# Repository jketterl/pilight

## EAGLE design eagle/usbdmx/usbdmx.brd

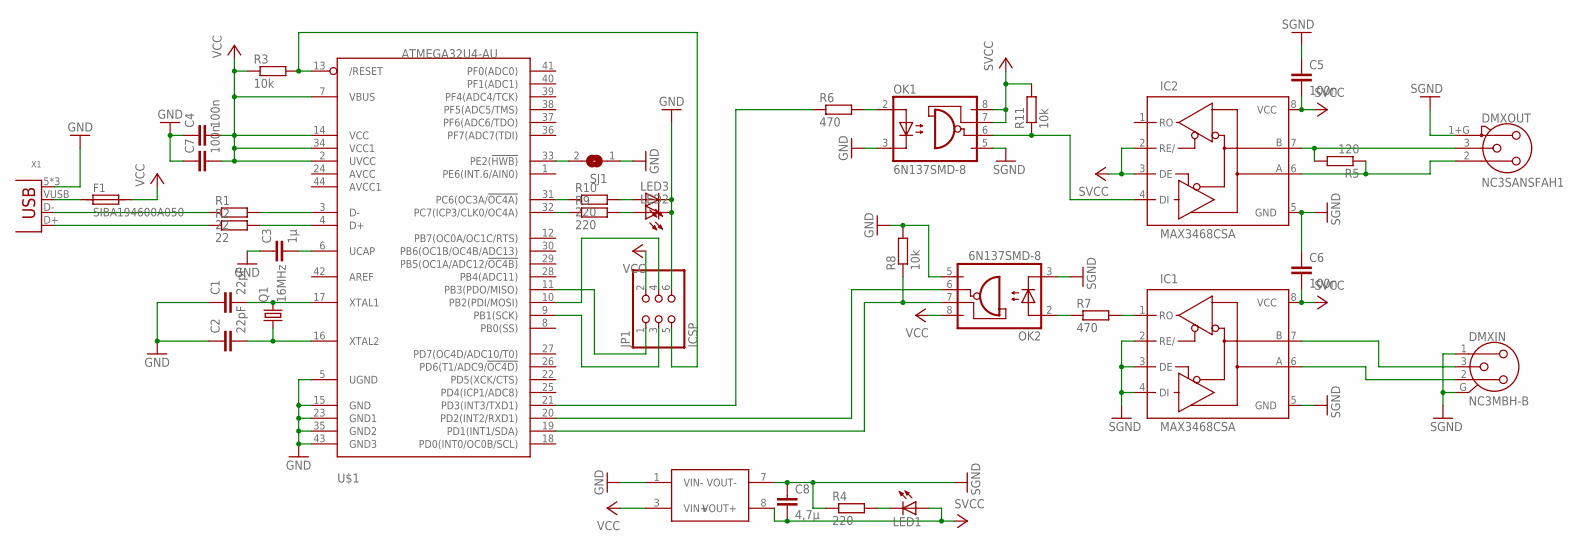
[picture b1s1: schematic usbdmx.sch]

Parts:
C1, C2: 22pF; C0805
C3: 1µ; C0805
C4, C5, C6, C7: 100n; C0805
C8: 4,7µ; C0805
DMXIN: NC3MBH-B
DMXOUT: NC3SANSFAH1; NC3FAH1
F1: SIBA194600A050; 1820
IC1, IC2: MAX3468CSA; SO08
JP1: ICSP; 2X03SMD
LED1, LED2, LED3: LEDSML0603; SML0603
OK1, OK2: 6N137SMD-8; SMD8
Q1: 16MHz; MT
R1, R2: 22; R0805
R3, R8, R11: 10k; R0805
R4, R9, R10: 220; R0805
R5: 120; R0805
R6, R7: 470; R0805
SJ1: SJ
U$1: ATMEGA32U4-AU; TQFP44
U$2: NTE0505SNTE0505MEC; SMT
X1: USB-B-S-R; USB-B-SMT-R

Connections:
GND: C1.1, C2.1, C3.1, C4.1, C7.1, JP1.6, LED2.C, LED3.C, OK1.3 (C), OK2.5 (GND), R8.2, SJ1.1, U$1.5 (UGND), U$1.15 (GND), U$1.23 (GND1), U$1.35 (GND2), U$1.43 (GND3), U$2.1 (VIN-), X1.5 (GND), X1.6 (GND), X1.GND
unnamed: C1.2, Q1.P3 (2), U$1.17 (XTAL1)
unnamed: C2.2, Q1.P1 (1), U$1.16 (XTAL2)
unnamed: R1.2, U$1.3 (D-)
unnamed: R2.2, U$1.4 (D+)
unnamed: R2.1, X1.D+
unnamed: R1.1, X1.D-
unnamed: F1.1, X1.VUSB (VBUS)
unnamed: C3.2, U$1.6 (UCAP)
unnamed: JP1.5, R3.2, U$1.13 (/RESET)
unnamed: R6.1, U$1.21 (PD3(INT3/TXD1))
unnamed: LED1.C, R4.2
unnamed: DMXOUT.2, IC2.6 (A), R5.1
unnamed: JP1.1, U$1.11 (PB3(PDO/MISO))
unnamed: JP1.4, U$1.10 (PB2(PDI/MOSI))
unnamed: JP1.3, U$1.9 (PB1(SCK))
unnamed: OK2.7 (VE), R8.1, U$1.19 (PD1(INT1/SDA))
unnamed: DMXOUT.3, IC2.7 (B), R5.2
unnamed: DMXIN.2, IC1.6 (A)
unnamed: SJ1.2, U$1.33 (PE2(!HWB))
unnamed: IC2.4 (DI), OK1.6 (VO), R11.1
unnamed: IC1.1 (RO), R7.2
unnamed: LED3.A, R10.2
unnamed: OK2.2 (A), R7.1
unnamed: OK2.6 (VO), U$1.20 (PD2(INT2/RXD1))
unnamed: OK1.2 (A), R6.2
unnamed: LED2.A, R9.2
unnamed: R9.1, U$1.32 (PC7(ICP3/CLK0/OC4A))
unnamed: R10.1, U$1.31 (PC6(OC3A/!OC4A))
unnamed: DMXIN.3, IC1.7 (B)
SGND: C5.1, C6.1, C8.1, DMXIN.1, DMXIN.G, DMXOUT.1+G (1), IC1.2 (RE/), IC1.3 (DE), IC1.4 (DI), IC1.5 (GND), IC2.5 (GND), OK1.5 (GND), OK2.3 (C), R4.1, U$2.7 (VOUT-)
SVCC: C5.2, C6.2, C8.2, IC1.8 (VCC), IC2.2 (RE/), IC2.3 (DE), IC2.8 (VCC), LED1.A, OK1.7 (VE), OK1.8 (VCC), R11.2, U$2.8 (VOUT+)
VCC: C4.2, C7.2, F1.2, JP1.2, OK2.8 (VCC), R3.1, U$1.2 (UVCC), U$1.7 (VBUS), U$1.14 (VCC), U$1.34 (VCC1), U$2.3 (VIN+)

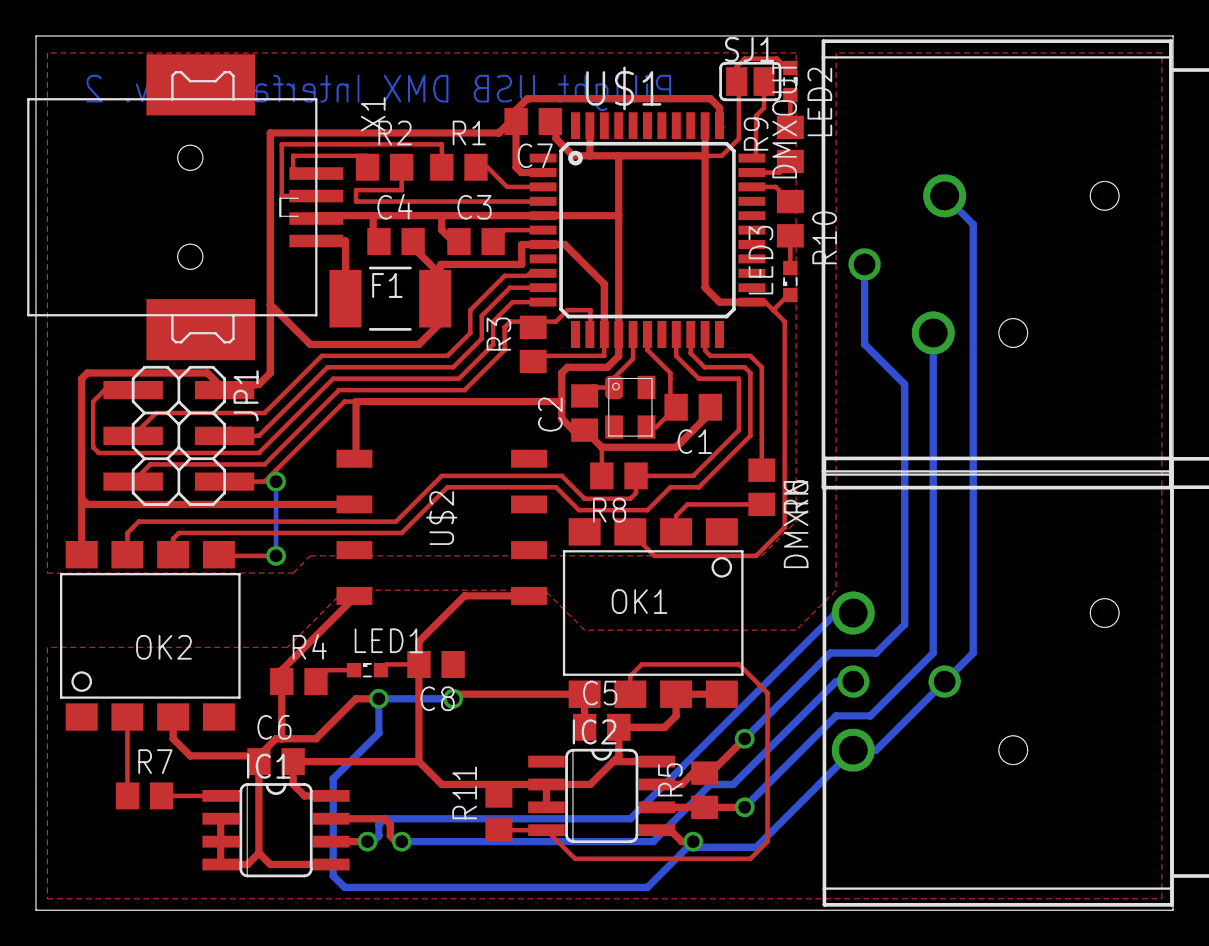
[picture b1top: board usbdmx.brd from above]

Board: 2 copper layers, 63.2 x 48.6 mm, 35 parts (0 on the bottom side), 33 nets.

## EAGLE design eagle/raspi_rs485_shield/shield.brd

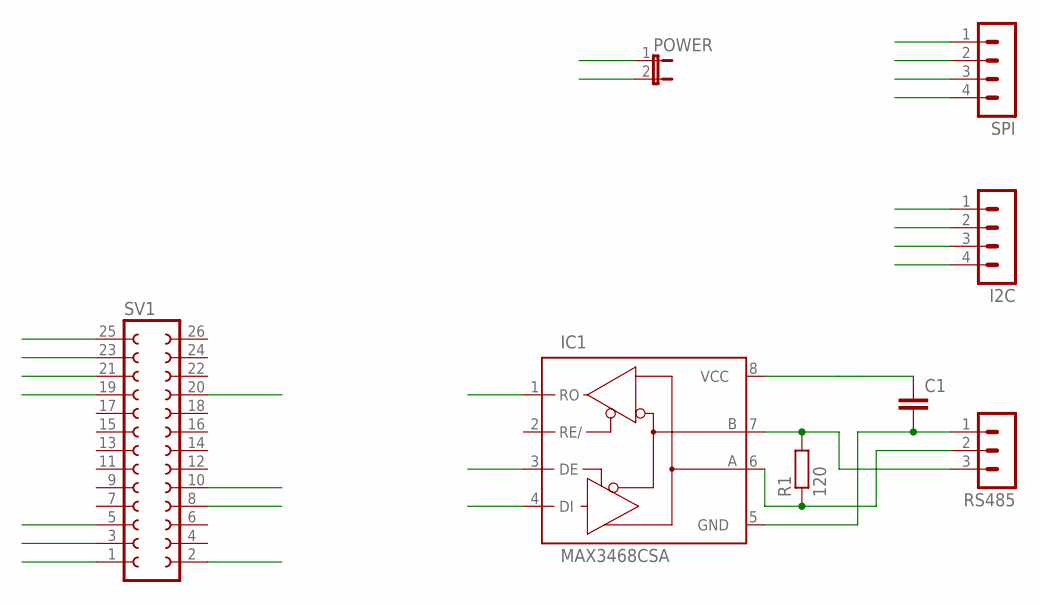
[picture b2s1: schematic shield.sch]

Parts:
C1: C-EUC0805; C0805
I2C: MA04-1
IC1: MAX3468CSA; SO08
POWER: JP1E; JP1
R1: 120; 0207/2V
RS485: MA03-1
SPI: MA04-1
SV1: FE13-2

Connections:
3V3: C1.1, IC1.3 (DE), IC1.8 (VCC), SV1.1
5V0: I2C.4, POWER.2, SV1.2
GND: C1.2, I2C.1, IC1.5 (GND), POWER.1, RS485.1, SPI.1, SV1.20, SV1.25
MISO: SPI.3, SV1.21
MOSI: SPI.2, SV1.19
unnamed: IC1.6 (A), R1.1, RS485.2
unnamed: IC1.7 (B), R1.2, RS485.3
RX: IC1.1 (RO), SV1.10
SCL: I2C.2, SV1.5
SCLK: SPI.4, SV1.23
SDA: I2C.3, SV1.3
TX: IC1.4 (DI), SV1.8

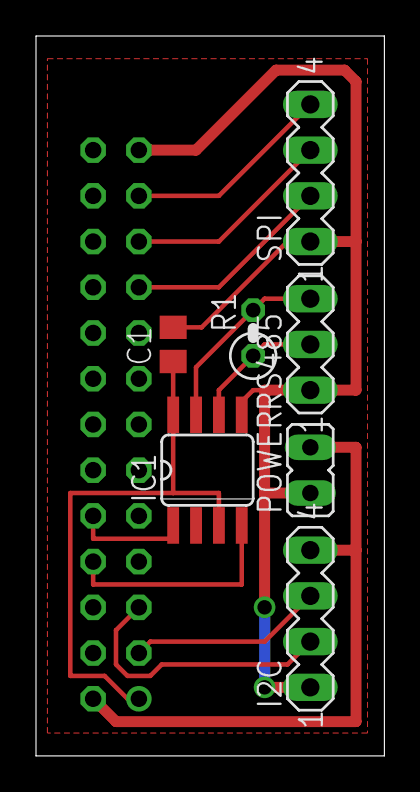
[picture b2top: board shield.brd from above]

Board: 2 copper layers, 19.4 x 40.0 mm, 8 parts (1 on the bottom side), 12 nets.

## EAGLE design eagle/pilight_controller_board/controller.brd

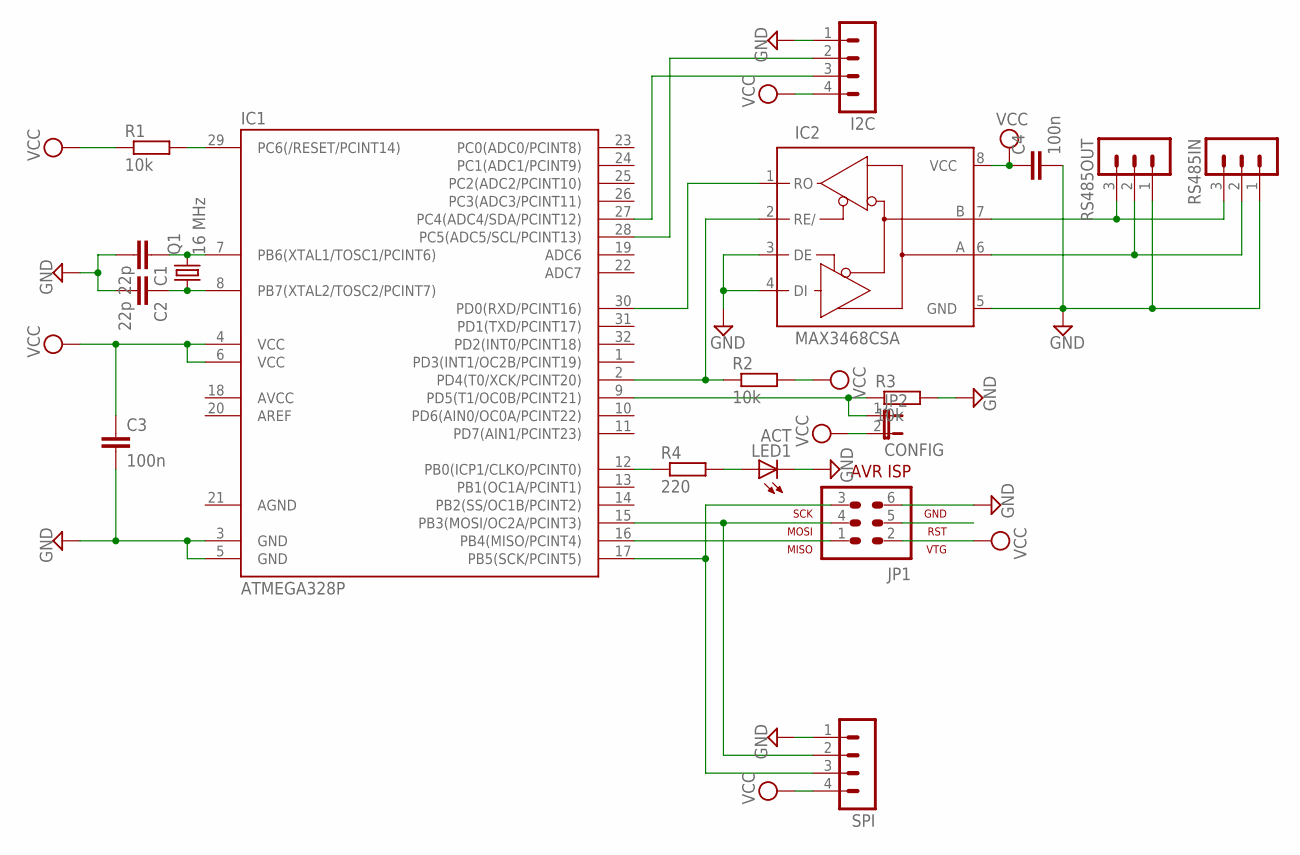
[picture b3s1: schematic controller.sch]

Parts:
C1, C2: 22p; C0805
C3, C4: 100n; C0805
I2C: MA04-1
IC1: ATMEGA328P; TQFP32-08
IC2: MAX3468CSA; SO08
JP1: AVR-ISP-6
JP2: CONFIG; JP1
LED1: ACT; SML0603
Q1: 16 MHz; MT
R1, R2, R3: 10k; R0805
R4: 220; R0805
RS485IN, RS485OUT: MA03-1
SPI: MA04-1

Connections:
AGND: IC1.21 (AGND)
GND: C1.2, C2.2, C3.2, C4.2, I2C.1, IC1.3 (GND), IC1.5 (GND), IC2.3 (DE), IC2.4 (DI), IC2.5 (GND), JP1.6, LED1.C, R3.2, RS485IN.1, RS485OUT.1, SPI.1
unnamed: IC1.30 (PD0(RXD/PCINT16)), IC2.1 (RO)
unnamed: IC1.15 (PB3(MOSI/OC2A/PCINT3)), JP1.4, SPI.2
unnamed: C1.1, IC1.7 (PB6(XTAL1/TOSC1/PCINT6)), Q1.P3 (2)
unnamed: C2.1, IC1.8 (PB7(XTAL2/TOSC2/PCINT7)), Q1.P1 (1)
unnamed: IC1.16 (PB4(MISO/PCINT4)), JP1.1
unnamed: IC1.17 (PB5(SCK/PCINT5)), JP1.3, SPI.3
unnamed: IC2.6 (A), RS485IN.2, RS485OUT.2
unnamed: IC2.7 (B), RS485IN.3, RS485OUT.3
unnamed: I2C.2, IC1.28 (PC5(ADC5/SCL/PCINT13))
unnamed: I2C.3, IC1.27 (PC4(ADC4/SDA/PCINT12))
unnamed: IC1.2 (PD4(T0/XCK/PCINT20)), IC2.2 (RE/), R2.1
unnamed: IC1.9 (PD5(T1/OC0B/PCINT21)), JP2.1, R3.1
unnamed: IC1.12 (PB0(ICP1/CLKO/PCINT0)), R4.1
unnamed: LED1.A, R4.2
RESET: IC1.29 (PC6(/RESET/PCINT14)), JP1.5, R1.2
VCC: C3.1, C4.1, I2C.4, IC1.4 (VCC), IC1.6 (VCC), IC2.8 (VCC), JP1.2, JP2.2, R1.1, R2.2, SPI.4

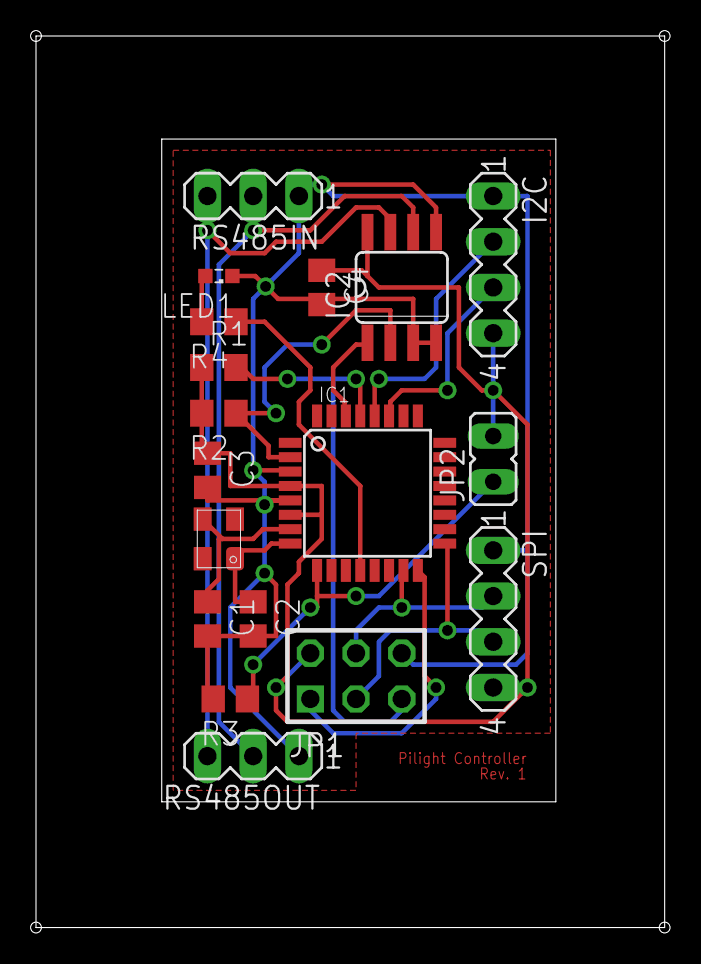
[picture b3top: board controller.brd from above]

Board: 2 copper layers, 34.9 x 49.5 mm, 18 parts (0 on the bottom side), 17 nets.

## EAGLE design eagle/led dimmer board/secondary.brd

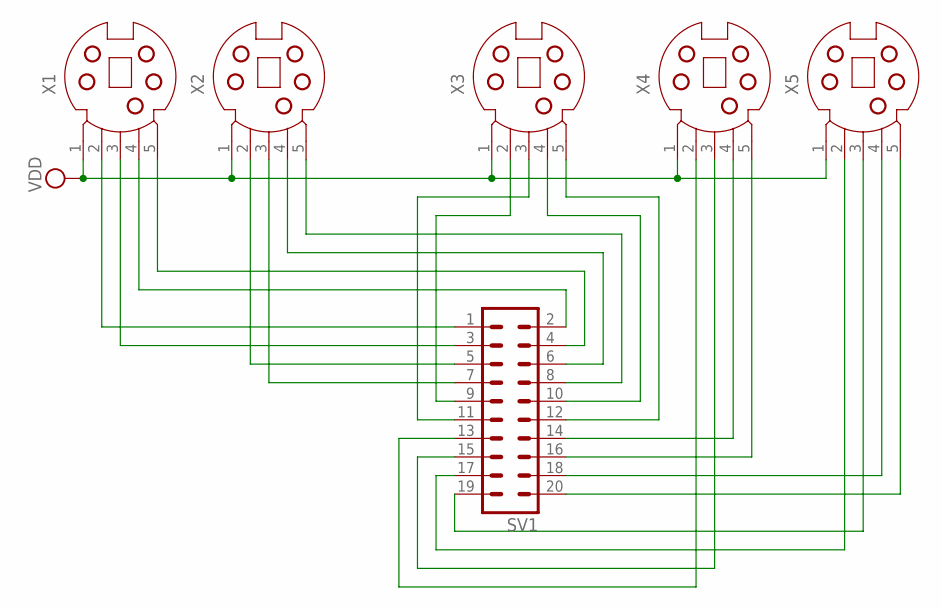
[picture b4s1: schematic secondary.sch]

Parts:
SV1: MA10-2
X1, X2, X3, X4, X5: MD05S; MDIN05S

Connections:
unnamed: SV1.1, X1.2
unnamed: SV1.2, X1.4
unnamed: SV1.3, X1.3
unnamed: SV1.4, X1.5
unnamed: SV1.5, X2.2
unnamed: SV1.6, X2.4
unnamed: SV1.7, X2.3
unnamed: SV1.8, X2.5
unnamed: SV1.9, X3.2
unnamed: SV1.10, X3.4
unnamed: SV1.11, X3.3
unnamed: SV1.12, X3.5
unnamed: SV1.14, X4.4
unnamed: SV1.16, X4.5
unnamed: SV1.18, X5.4
unnamed: SV1.20, X5.5
unnamed: SV1.19, X5.3
unnamed: SV1.17, X5.2
unnamed: SV1.15, X4.3
unnamed: SV1.13, X4.2
VDD: X1.1, X2.1, X3.1, X4.1, X5.1

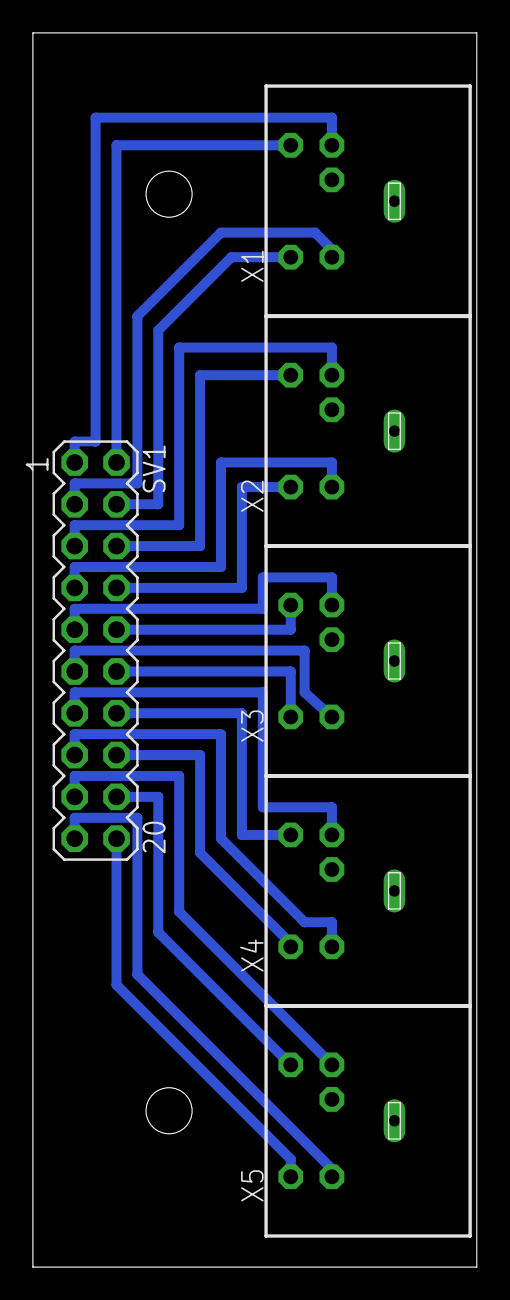
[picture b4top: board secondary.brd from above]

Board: 2 copper layers, 27.0 x 75.0 mm, 6 parts (0 on the bottom side), 21 nets.

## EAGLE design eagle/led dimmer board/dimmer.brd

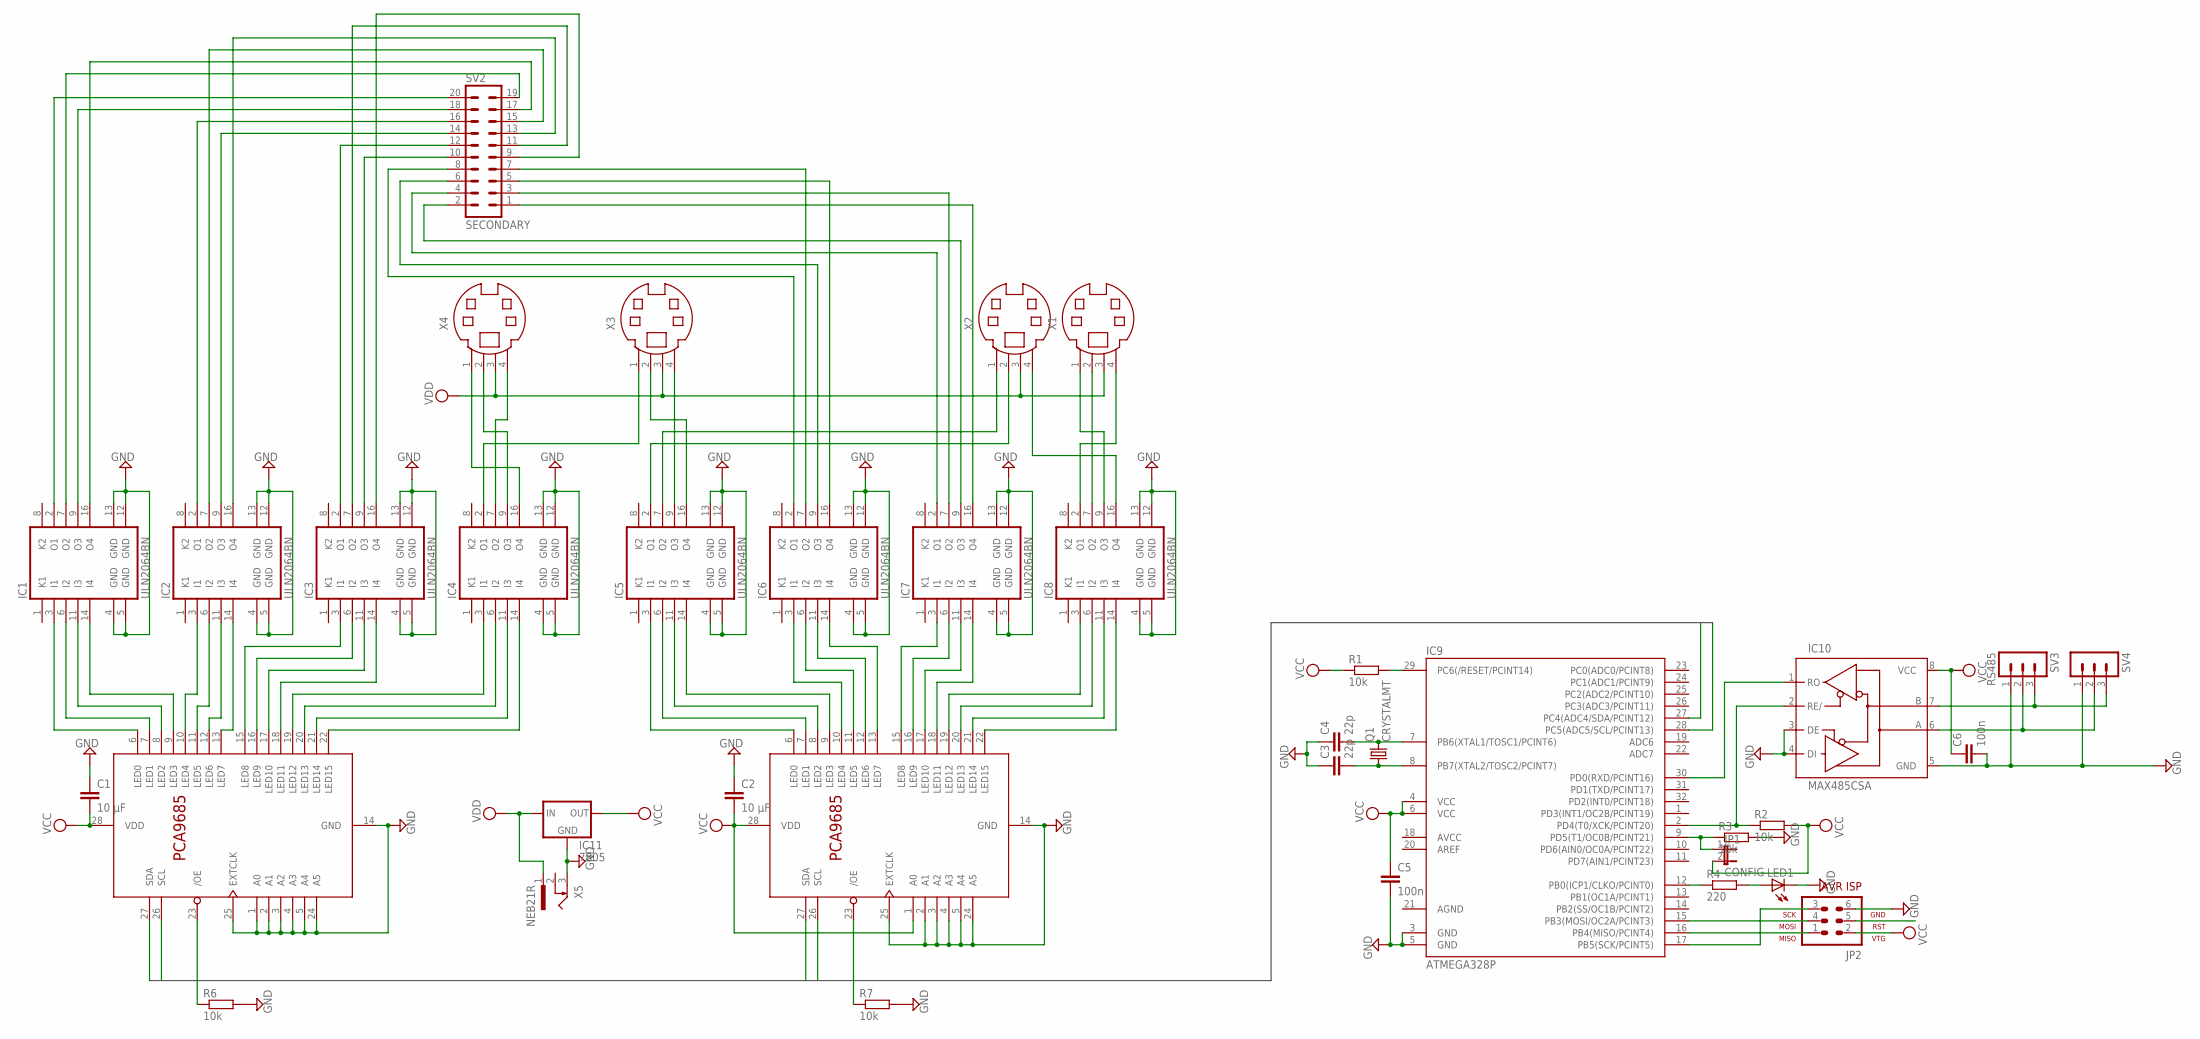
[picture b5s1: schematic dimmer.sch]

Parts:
C1, C2: 10 µF; C0805
C3, C4: 22p; C0805
C5, C6: 100n; C0805
IC1, IC2, IC3, IC4, IC5, IC6, IC7, IC8: ULN2064BN; DIL16
IC9: ATMEGA328P; TQFP32-08
IC10: MAX485CSA; SO08
IC11: 7805; 78XXS
JP1: CONFIG; JP1
JP2: AVR-ISP-6
LED1: LEDCHIP-LED0603; CHIP-LED0603
Q1: CRYSTALMT; MT
R1, R2, R3, R6, R7: 10k; R0805
R4: 220; R0805
SV2: SECONDARY; MA10-2
SV3: RS485; MA03-1
SV4: MA03-1
U$1, U$2: PCA9685PW; TSSOP28
X1, X2, X3, X4: MD04S; MDIN04S
X5: NEB21R

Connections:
AGND: IC9.21 (AGND)
GND: C1.1, C2.1, C3.1, C4.1, C5.2, C6.2, IC1.4 (GND), IC1.5 (GND), IC1.12 (GND), IC1.13 (GND), IC2.4 (GND), IC2.5 (GND), IC2.12 (GND), IC2.13 (GND), IC3.4 (GND), IC3.5 (GND), IC3.12 (GND), IC3.13 (GND), IC4.4 (GND), IC4.5 (GND), IC4.12 (GND), IC4.13 (GND), IC5.4 (GND), IC5.5 (GND), IC5.12 (GND), IC5.13 (GND), IC6.4 (GND), IC6.5 (GND), IC6.12 (GND), IC6.13 (GND), IC7.4 (GND), IC7.5 (GND), IC7.12 (GND), IC7.13 (GND), IC8.4 (GND), IC8.5 (GND), IC8.12 (GND), IC8.13 (GND), IC9.3 (GND), IC9.5 (GND), IC10.3 (DE), IC10.4 (DI), IC10.5 (GND), IC11.GND, JP2.6, LED1.C, R3.2, R6.2, R7.2, SV3.1, SV4.1, U$1.1 (A0), U$1.2 (A1), U$1.3 (A2), U$1.4 (A3), U$1.5 (A4), U$1.14 (GND), U$1.24 (A5), U$1.25 (EXTCLK), U$2.2 (A1), U$2.3 (A2), U$2.4 (A3), U$2.5 (A4), U$2.14 (GND), U$2.24 (A5), U$2.25 (EXTCLK), X5.3
unnamed: IC1.3 (I1), U$1.6 (LED0)
unnamed: IC1.6 (I2), U$1.7 (LED1)
unnamed: IC1.11 (I3), U$1.8 (LED2)
unnamed: IC1.14 (I4), U$1.9 (LED3)
unnamed: IC4.14 (I4), U$1.22 (LED15)
unnamed: IC4.11 (I3), U$1.21 (LED14)
unnamed: IC4.6 (I2), U$1.20 (LED13)
unnamed: IC4.3 (I1), U$1.19 (LED12)
unnamed: IC3.14 (I4), U$1.18 (LED11)
unnamed: IC3.11 (I3), U$1.17 (LED10)
unnamed: IC3.6 (I2), U$1.16 (LED9)
unnamed: IC3.3 (I1), U$1.15 (LED8)
unnamed: IC2.14 (I4), U$1.13 (LED7)
unnamed: IC2.11 (I3), U$1.12 (LED6)
unnamed: IC2.6 (I2), U$1.11 (LED5)
unnamed: IC2.3 (I1), U$1.10 (LED4)
unnamed: IC7.14 (I4), U$2.18 (LED11)
unnamed: IC5.6 (I2), U$2.7 (LED1)
unnamed: IC5.11 (I3), U$2.8 (LED2)
unnamed: IC5.14 (I4), U$2.9 (LED3)
unnamed: IC5.3 (I1), U$2.6 (LED0)
unnamed: IC6.3 (I1), U$2.10 (LED4)
unnamed: IC6.6 (I2), U$2.11 (LED5)
unnamed: IC6.11 (I3), U$2.12 (LED6)
unnamed: IC6.14 (I4), U$2.13 (LED7)
unnamed: IC8.14 (I4), U$2.22 (LED15)
unnamed: IC8.11 (I3), U$2.21 (LED14)
unnamed: IC8.6 (I2), U$2.20 (LED13)
unnamed: IC8.3 (I1), U$2.19 (LED12)
unnamed: IC7.11 (I3), U$2.17 (LED10)
unnamed: IC7.6 (I2), U$2.16 (LED9)
unnamed: IC7.3 (I1), U$2.15 (LED8)
unnamed: IC8.2 (O1), X1.4
unnamed: IC8.7 (O2), X1.2
unnamed: IC8.9 (O3), X1.1
unnamed: R6.1, U$1.23 (/OE)
unnamed: IC8.16 (O4), X2.4
unnamed: IC5.2 (O1), X2.2
unnamed: IC5.7 (O2), X2.1
unnamed: IC5.9 (O3), X3.4
unnamed: IC5.16 (O4), X3.2
unnamed: IC4.2 (O1), X3.1
unnamed: IC4.7 (O2), X4.4
unnamed: IC4.9 (O3), X4.2
unnamed: IC4.16 (O4), X4.1
unnamed: IC1.2 (O1), SV2.20
unnamed: IC1.7 (O2), SV2.19
unnamed: IC1.9 (O3), SV2.18
unnamed: IC1.16 (O4), SV2.17
unnamed: IC2.2 (O1), SV2.16
unnamed: IC2.7 (O2), SV2.15
unnamed: IC2.9 (O3), SV2.14
unnamed: IC2.16 (O4), SV2.13
unnamed: IC3.2 (O1), SV2.12
unnamed: IC3.7 (O2), SV2.11
unnamed: IC3.9 (O3), SV2.10
unnamed: IC3.16 (O4), SV2.9
unnamed: IC6.2 (O1), SV2.8
unnamed: IC6.7 (O2), SV2.7
unnamed: IC6.9 (O3), SV2.6
unnamed: IC6.16 (O4), SV2.5
unnamed: IC7.2 (O1), SV2.4
unnamed: IC7.7 (O2), SV2.3
unnamed: IC7.9 (O3), SV2.2
unnamed: IC7.16 (O4), SV2.1
unnamed: R7.1, U$2.23 (/OE)
unnamed: C4.2, IC9.7 (PB6(XTAL1/TOSC1/PCINT6)), Q1.P3 (2)
unnamed: IC9.30 (PD0(RXD/PCINT16)), IC10.1 (RO)
unnamed: C3.2, IC9.8 (PB7(XTAL2/TOSC2/PCINT7)), Q1.P1 (1)
unnamed: IC10.6 (A), SV3.2, SV4.2
unnamed: IC10.7 (B), SV3.3, SV4.3
unnamed: IC9.2 (PD4(T0/XCK/PCINT20)), IC10.2 (RE/), R2.1
unnamed: IC9.9 (PD5(T1/OC0B/PCINT21)), JP1.1, R3.1
unnamed: IC9.12 (PB0(ICP1/CLKO/PCINT0)), R4.1
unnamed: LED1.A, R4.2
unnamed: IC9.17 (PB5(SCK/PCINT5)), JP2.3
unnamed: IC9.16 (PB4(MISO/PCINT4)), JP2.1
unnamed: IC9.15 (PB3(MOSI/OC2A/PCINT3)), JP2.4
RESET: IC9.29 (PC6(/RESET/PCINT14)), JP2.5, R1.2
SCL: IC9.28 (PC5(ADC5/SCL/PCINT13)), U$1.26 (SCL), U$2.26 (SCL)
SDA: IC9.27 (PC4(ADC4/SDA/PCINT12)), U$1.27 (SDA), U$2.27 (SDA)
VCC: C1.2, C2.2, C5.1, C6.1, IC9.4 (VCC), IC9.6 (VCC), IC10.8 (VCC), IC11.OUT, JP1.2, JP2.2, R1.1, R2.2, U$1.28 (VDD), U$2.1 (A0), U$2.28 (VDD)
VDD: IC11.IN, X1.3, X2.3, X3.3, X4.3, X5.1

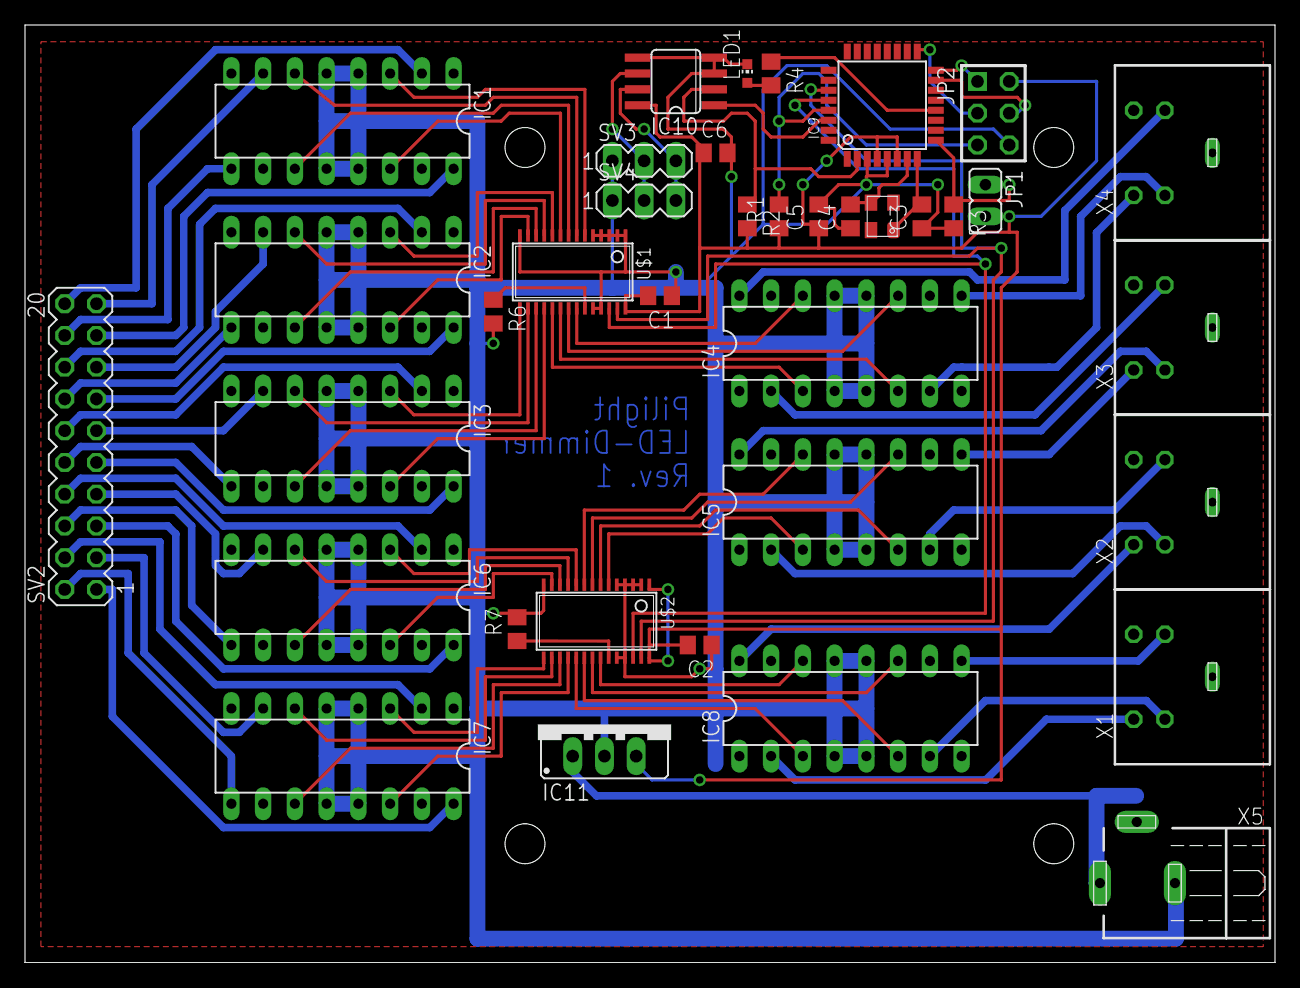
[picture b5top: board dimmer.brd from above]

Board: 2 copper layers, 100.0 x 75.0 mm, 37 parts (0 on the bottom side), 84 nets.

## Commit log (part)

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2012-11-07 initial import
2012-11-15 constructing an output module
2012-11-15 threaded output prototype
2012-11-15 drop the changes once written
2012-11-16 adding LPD8806 support
2012-11-16 add flush to make it work
2012-11-16 let's get some action :)
2012-11-16 fix typos
2012-11-16 fix channel count
2012-11-16 add the knight rider
2012-11-18 test for "None" value before pushing changes out
2012-11-18 write out some extra zeros to flush
2012-11-18 add snowflakes :)
2012-11-18 fix indentation
2012-11-19 implement the knight rider OOP
2012-11-19 add new VU Meter show
2012-11-19 move to the right location
2012-11-19 fix colors
2012-11-19 trying to get the vu meter running
2012-11-19 fixing audio reading by putting it into a background thread
2012-11-20 performance optimizing the vu meter
2012-11-20 make the vu meter smoother by introducing a smoothing thread
2012-11-20 commit uncomplete changes (so far, so good)
2012-11-20 lots of changes to improve the vu meter (better refresh rate, improved smoothin)
2012-11-21 refactor: create audio module & move the audioreader over
2012-11-21 move over the analyzer too
2012-11-21 no longer a show object
2012-11-21 simulating a bpm show (with constant "heartbeat" as bpm)
2012-11-21 integrate bpm show
2012-11-21 move sanity check to the reader
2012-11-21 clean up after show end
2012-11-21 incomplete beat detection
2012-11-22 fix a potential issue with empty data
2012-11-22 refactor audioreader to be reusable
2012-11-22 fixed beatdetection (unpacked wrong)
2012-11-23 fft-based beat-detection, phase 1
2012-11-25 fiddling with the BeatDetector code implementing first steps with lirc
2012-11-25 further lirc control
2012-11-25 more shows
2012-11-25 multi-key-mapping standby code
2012-11-25 add the fixtures parameter as a default to all shows
2012-11-25 re-implement the snowflake show as a show
2012-11-25 ignore compiled python files
2012-11-25 faster clearup interval (in case of disturbances)
2012-11-25 adding a new show to cycle through some colors
2012-11-25 pre-calculate sleep times during fades to reduce load
2012-11-28 adding the alpha filter (and basic filtering ability for the universe clase)
2012-12-02 adding structure for the artnet output
2012-12-02 import the right module
2012-12-02 module cleanup
2012-12-02 make modifications to the search path to allow importing artnet libraries
2012-12-03 adding logarithmic bands for beat detection
2012-12-03 implement artnet output
2012-12-03 adding adafruit vendor files
2012-12-03 implement pwm output module
2012-12-03 first steps implementing the artnet input
2012-12-03 complete implementation of artnet input
2012-12-03 vendor update
2012-12-05 make feedback faster by only sending channels that have been changed
2012-12-05 implement beat detection variance
2012-12-15 added a new FFT analyzer show
2012-12-15 make the snow show clean itself up
2012-12-15 make the color wheel show clean itself up
2012-12-15 make the colorfader show clean itself up
2012-12-16 allow direct mapping against universes (using an offset)
2012-12-18 init the necessary variables before starting the background thread
2012-12-18 build a back-channel from the browser to the server, to simulate lirc input or similiar
2012-12-18 add a getter for the value
2012-12-19 adding the new submaster module to allow controlling mapped channel values
2012-12-19 break apart into separate files for easier maintenance
2012-12-19 add a master channel
2012-12-19 make everything work in the real environment again
2012-12-23 add dj lighting (separate from show logic)
2012-12-23 performance improvements for the fft show
2012-12-23 reduce the amount of event.set() calls to improve performance (slightly)
2012-12-23 well that did not quite work out. fixing output again
2012-12-25 adding code to shutdown outputs properly
2012-12-25 improve performance by reducing the amount of necessary calculations
2012-12-25 trying to increase performance further by reducing the amount of necessary array transformations
2012-12-25 reduce to audible frequencies (reduces ghost values, and also increases performance)
2012-12-25 the new optimized output allows a faster & super-smooth color wheel :)
2012-12-25 modify the VU output to accept values from 0..1
2012-12-25 allow external configuration of colors for the VU outpu
2012-12-25 color the fft show in nice blue & red
2012-12-25 rewritten to use the FFTReader
2012-12-28 adding an lcdproc message on channel selection
2012-12-29 adding a filter to scale only
2012-12-31 use the messenger in the showrunner, too
2012-12-31 adding an idle screen with the backlight off
2012-12-31 select the master channel by default (to avoid exceptions when up/down is pressed before a channel is selcted)
2013-01-09 add a way to get every update on a channel
2013-01-09 adding a colorful strobe show
2013-01-11 add the CombFilter work so far
2013-01-11 add a real strobe show
2013-01-11 add new full / off buttons to the submaster
2013-06-08 add support for WS2801 chip driven led strips
2013-06-09 add the new multi-channel-mapping
2013-06-09 introduce variable channel sequence for rgb devices
2013-06-09 fix channel mapping for strobe
2013-06-09 adding the new pixel leds on pilight03
2013-06-14 adjust timing
2013-06-14 implementing a custom protocol over TCP to get low-latency high-throughput client connections
2013-06-14 trying to improve udp by enforcing the socket to send all data
2013-06-14 implement TCP protocol (client side)
2013-08-01 move simulator to make space for new web interface
2013-08-01 add first steps for an ext.js based web frontend
2013-08-01 reuse socket
2013-08-01 preparation work for browser control
2013-08-01 remove stupid vi swap file
2013-08-01 first remote-controlled module available: submaster
2013-08-01 add a show control frontend & implement show start & stop
2013-08-01 add non-audio shows
2013-08-01 add missing files align windows (preliminary)
2013-08-01 start show on double click
2013-08-02 make bpm strobe blips beautiful
2013-08-02 add police show
2013-08-02 add more randomness
2013-08-04 handle a few potential problems
2013-08-04 print exception (so that we have the chance to see something)
2013-08-04 backport show control to the main system
2013-08-06 generate ui elements dynamically
2013-08-06 add state for the frontend
2013-08-06 make the submaster faders move remotely
2013-08-06 disconnect listeners when socket closes
2013-08-06 feedback for the showrunner, too
2013-08-06 socket input for pwmslave
2013-08-06 catch socket errors to allow reconnects
2013-08-06 restore values from last time on gui connect
2013-08-06 sync the last known state for the showrunner, too
2013-08-06 remove console.info
2013-08-06 allow dynamic addition of controllables allow colorwheel parameters to be customized
2013-08-06 add a speed control
2013-08-08 add flash buttons
2013-08-14 add messageing to the frontend
2013-08-14 rewritten submaster panel to use a new controllable backend object
2013-08-27 bands as instance variable
2013-08-29 pass fixtures (necessary)
2013-08-29 adding Twinkle show
2013-09-03 adding serial output for RS485 connections
2013-09-03 addding "Dimmer" fixture for regular lights
2013-09-03 allow multiple outputs to be written over a single serial line
2013-09-03 wiring the pixels via RS485, yay!
2013-09-03 fix direct fft shutdown
2013-09-04 fix direct fft shutdown again (leave no background threads behind)
2013-09-08 send full frames over serial output if timeout occures
2013-09-11 switch to the new led dimmer
2013-09-11 make green twinkles :)
2013-09-12 send alpha frames instead of delta frames when they are smaller fix alpha frame bug where old data was being sent
2013-09-17 rewire dj lights to the led dimmer
2013-09-30 vu meter fixes
2013-09-30 preliminary midi support
2013-10-07 add wake-up light
2013-12-23 separate wakelight show & modified wakeup time
2013-12-23 fix band #
2013-12-23 xmas features
2014-03-30 add twinkle show
2014-03-30 add lichterkette show
2014-03-30 add lichterkette to standalone
2014-03-31 replace the fixture array with a fixture manager & querying
2014-03-31 use the new tagging system to generate submaster channels
2014-08-15 tags update for standalone mode
2014-11-06 adding recent work on an android app
2014-11-06 refactor & collect classes
2014-11-06 wait for command result before seding next command create some helper code for sending commands to the server
2014-11-06 implement basic list of shows
2014-11-06 stopping shows
2014-11-06 updates for the server for the submaster
2014-11-06 stop multi-listening
2014-11-06 block updates while the submaster is in use
2014-11-07 implement showmanager updates
2014-12-26 add eagle files
2015-01-13 add usbdmx vendor submodule
2015-01-13 new christmas setup
2015-01-13 add some sample dmx channels
2015-01-13 fix direct fft show
2015-01-14 add the new led pars
2015-01-14 add a new bpm-controlled show to show off the led pars
2015-01-19 remove christmas lights
2015-01-19 put fft on pars
2015-01-19 unmodified arduino core
2015-01-19 add core modifications so far
2015-01-19 add board definition excerpt
2015-01-19 add arduino sketch
2015-01-20 add new board design (unfinished)
2015-01-24 simple layout without galvanic isolation
2015-01-25 complete design with optocouplers and dc-dc-transformer for galvanic isolation
2015-01-25 invert outputs due to optocoupler
2015-01-26 rewire
2015-01-27 rewire some components to improve isolation
2015-01-28 replace the optocoupler package
2015-01-28 add a solder pad to enable the boot loader
2015-01-29 make design smaller since the neutriks can be put closer
2015-02-02 add a necessary pull-up
2015-02-09 add text
2015-02-10 fix the polarity mixup on the secondary side
2015-02-10 add postscript files
2015-02-10 increment revision number
2015-02-11 ignore ext files
2015-02-11 add status light
2015-02-17 add mode switching
2015-02-17 add arduino code
2015-02-17 avoid double init
2015-02-19 run on pixels again
2015-02-20 multi-show
2015-02-20 add show pre-filtering in show manager
2015-02-20 submovers specific changes
2015-03-03 improve exception output
2015-03-03 remove messaging from showrunner
2015-03-03 improved show api
2015-03-03 add "stop all shows" button to ui
2015-03-03 update to latest show api; make the stop button on the remote work again
2015-06-28 add dmx pixels
2015-07-12 introduce a connection window
2015-07-12 always disable loading mask (helpful when server is not up)
2015-07-12 make it pretty
2015-09-15 add new show for balcony
2015-09-15 preliminary fix vu show
2015-09-15 some more stuff on the UI
2015-10-26 fix ParBlip show
2015-12-18 config for weihnachtsfeier
2015-12-18 add button capability
2015-12-18 update main config
2015-12-18 add remote mappings
2015-12-18 add more remote mapping capabilities
2015-12-18 allow brightness changes on the fly
2015-12-19 fix indexerror
2015-12-19 allow multiple channels to be mapped for a single show
2015-12-19 add output mappings
2015-12-19 add remote output channels
2015-12-19 remove debugging
2015-12-20 rename bank properties
2015-12-20 add FX mappings
2015-12-21 add the xmas tree setup
2015-12-21 fix colorwheel ui
2015-12-25 add more xmas shows
2015-12-25 send bank name to remote
2015-12-25 allow multiple submasters
2015-12-25 fix exception when remote connects too early
2015-12-25 fix submaster frontend code for multiple instances
2015-12-27 add gpio input for light switch control
2015-12-27 use gpio interrupts to avoid polling loops
2015-12-27 work on the pilight system shutdown
2016-01-04 add new flags required by newer arduino ide
2016-01-09 fix artnet broadcast
2016-01-10 remove xmas tree & add new artnet controlled photon led pixels
2016-03-07 allow artnet universes to be set
2016-04-03 android studio upgrade
2016-04-03 add widget that allows switching submaster channels from the homescreen
2016-11-27 automatically find artnet devices by broadcast
2016-11-27 fix knightrider show
2016-11-27 submodule update
2016-12-08 artnet: don't break on unreachable host; fix number of channels
2016-12-10 home config updates
2017-02-24 update to latest android studio
2018-05-19 add aws lambda function
